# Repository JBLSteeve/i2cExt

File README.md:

# i2cExt
# 
# Jeedom plugin for XplDuino boards
# 	based on IPX800 design
# 	based on JeePlcBus daemon
# 
# Thanks to Ikes7200 and PFrank1990

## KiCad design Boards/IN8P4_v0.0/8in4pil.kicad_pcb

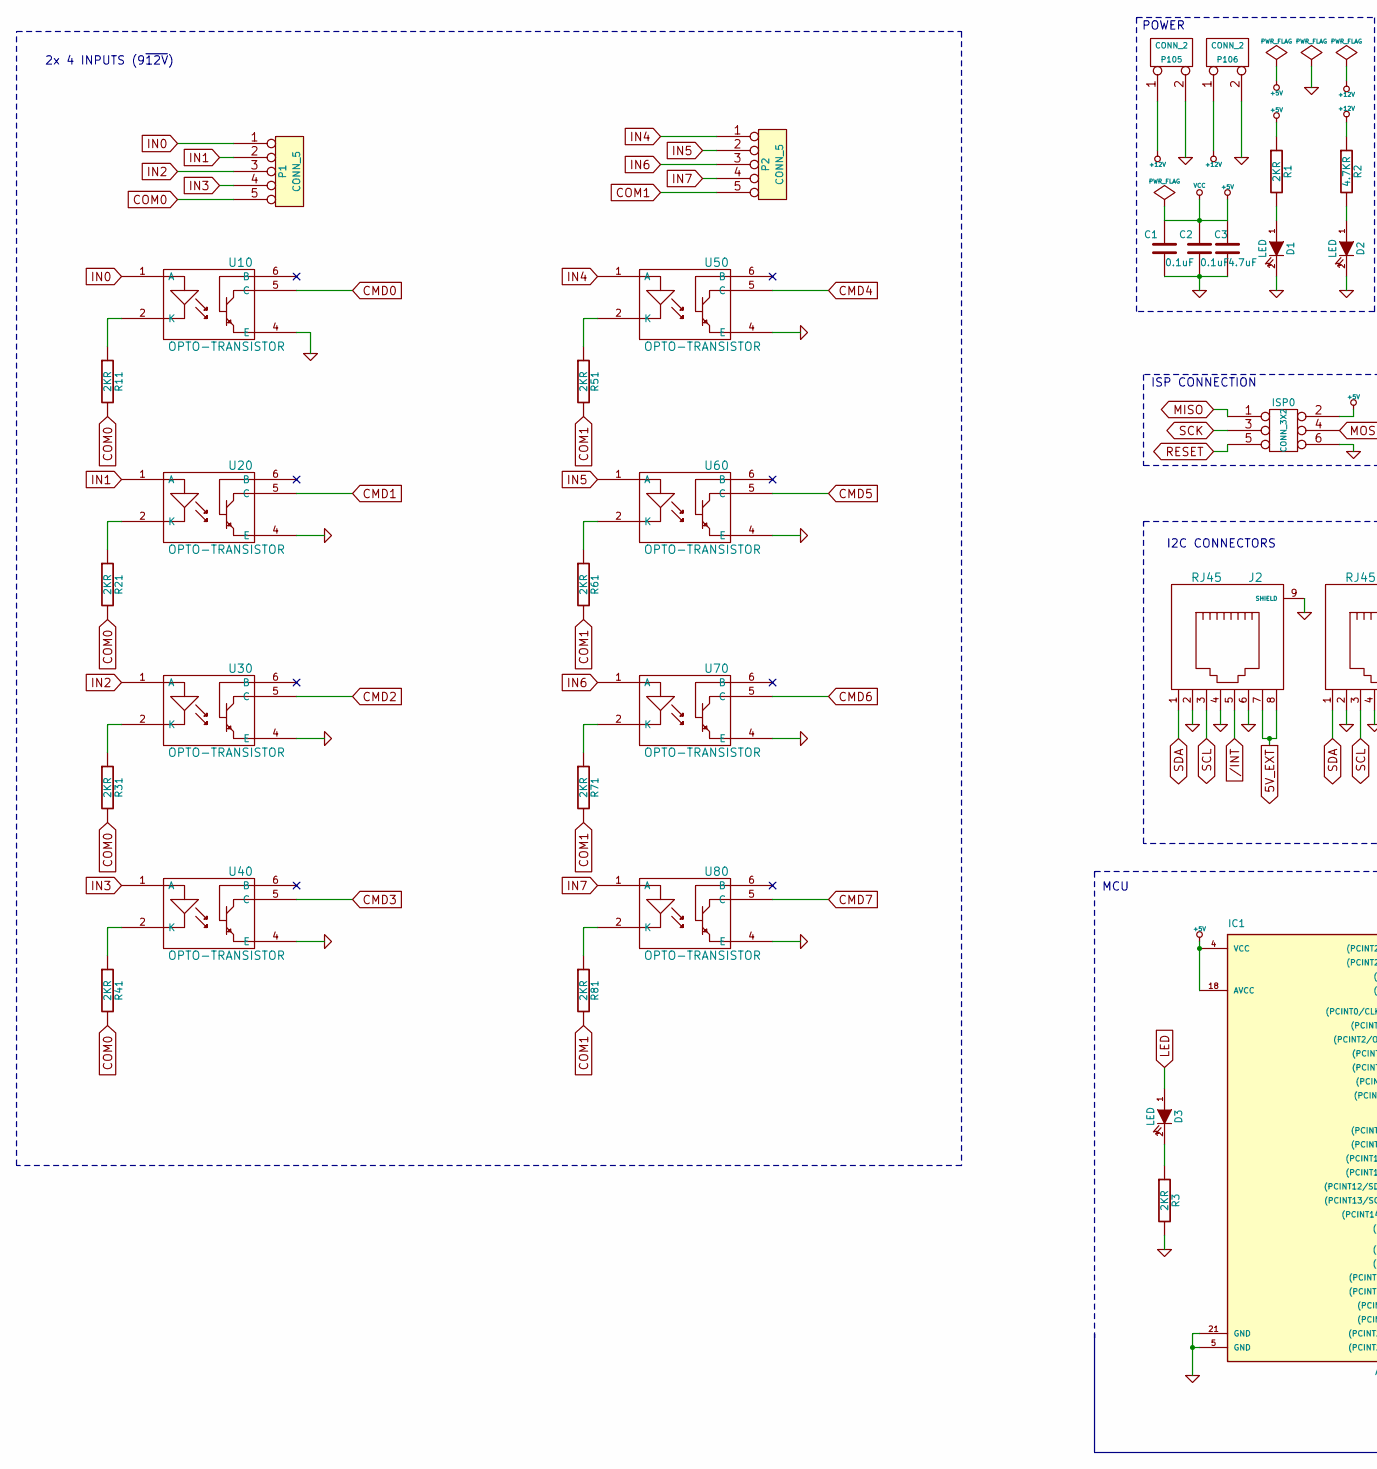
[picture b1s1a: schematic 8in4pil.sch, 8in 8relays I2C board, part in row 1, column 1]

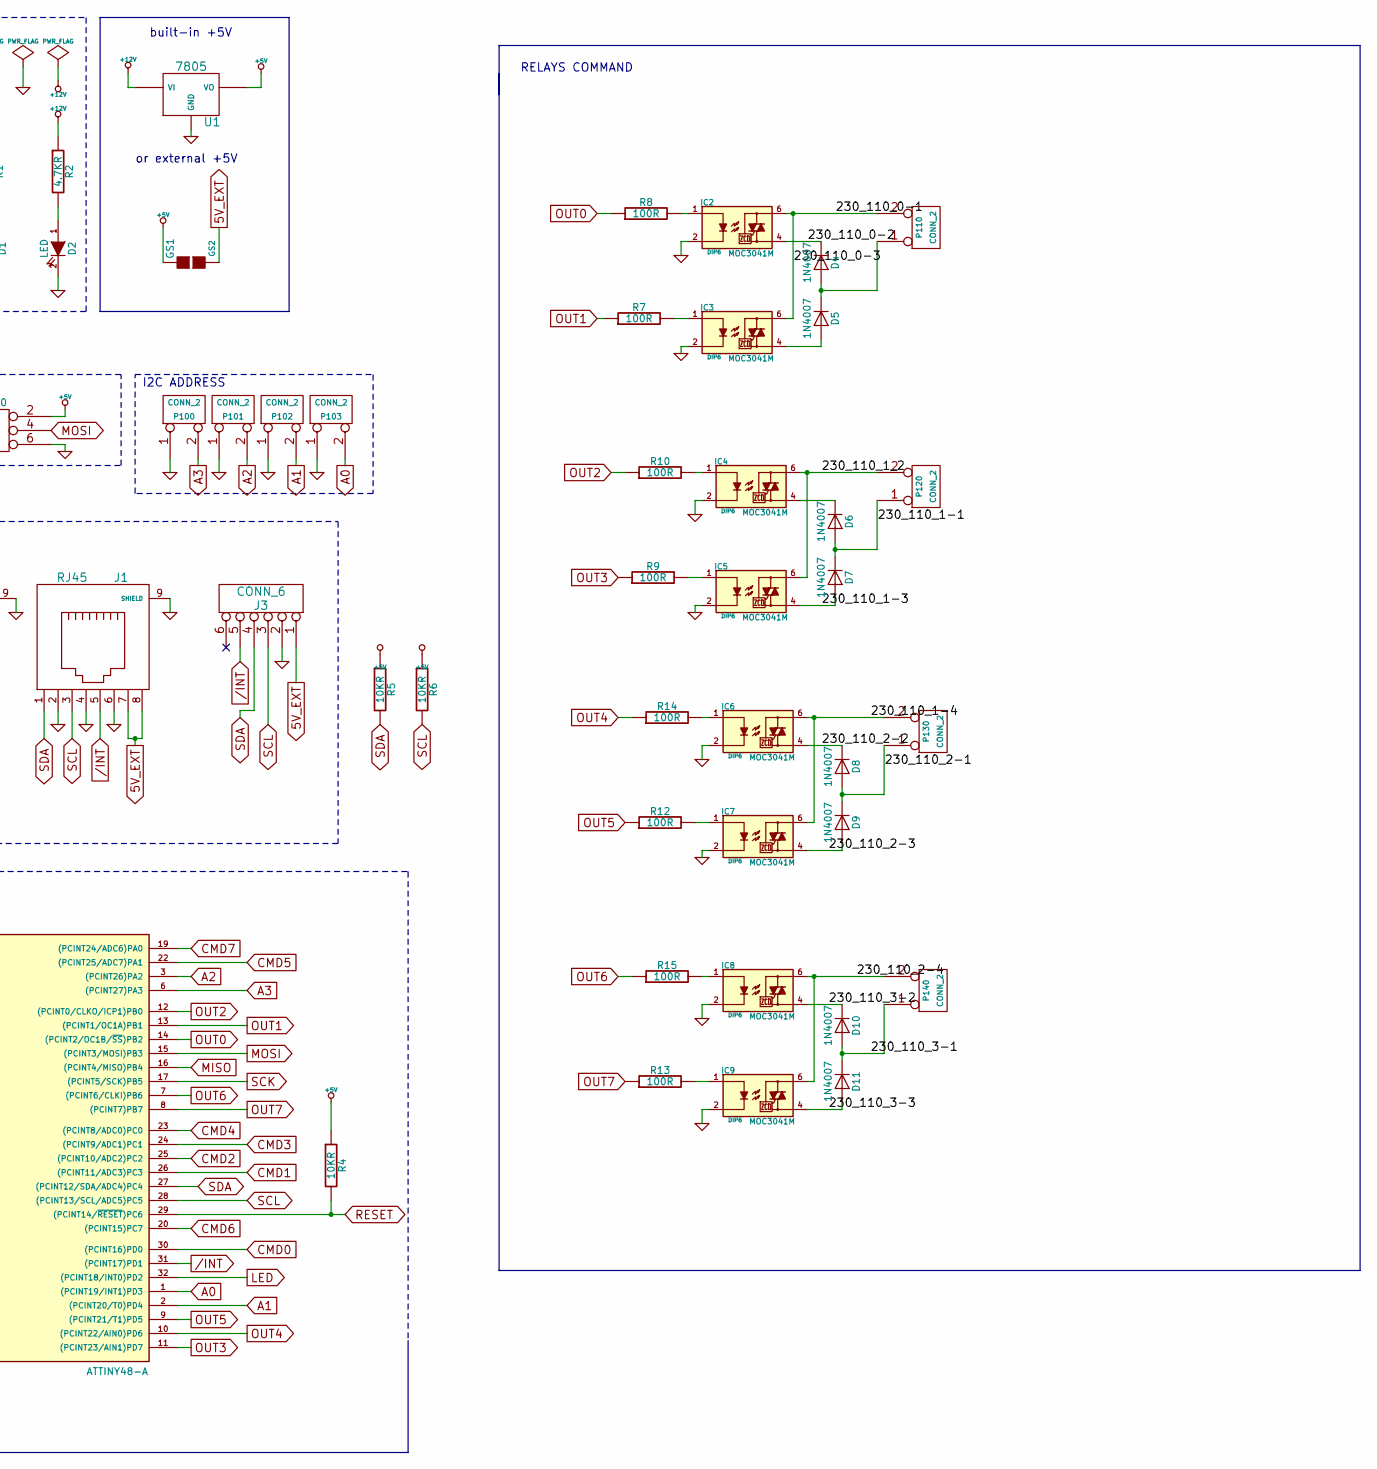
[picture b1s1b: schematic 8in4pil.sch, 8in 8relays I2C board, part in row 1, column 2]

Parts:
C1, C2: 0.1uF
C3: 4.7uF
D1, D2, D3: LED
D4, D5, D6, D7, D8, D9, D10, D11: 1N4007; D_DO-41_SOD81_P10.16mm_Horizontal
GS1: GS2
IC1: ATTINY48-A; TQFP32
IC2, IC3, IC4, IC5, IC6, IC7, IC8, IC9: MOC3041M; DIP6
ISP0: CONN_3X2
J1, J2: RJ45
J3: CONN_6
P1, P2: CONN_5
P100, P101, P102, P103, P105, P106, P110, P120, P130, P140: CONN_2
R1, R3, R11, R21, R31, R41, R51, R61, R71, R81: 2KR
R2: 4.7KR
R4, R5, R6: 10KR
R7, R8, R9, R10, R12, R13, R14, R15: 100R
U1: 7805
U10, U20, U30, U40, U50, U60, U70, U80: OPTO-TRANSISTOR

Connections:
5V_EXT: GS1.2 (G2), J1.7, J1.8, J2.7, J2.8, J3.1
+5V: C1.1, C2.1, C3.1, GS1.1 (G1), IC1.4 (VCC), IC1.18 (AVCC), ISP0.2, R1.1, R4.1, R5.1, R6.1, U1.VO
+12V: P105.1, P106.1, R2.1, U1.VI
/230_110_0-1: IC2.6, IC3.6, P110.2 (PM)
/230_110_0-2: D4.1 (K), IC2.4
/230_110_1-1: D6.2 (A), D7.1 (K), P120.1
/230_110_1-3: D7.2 (A), IC5.4
/230_110_1-4: IC6.6, IC7.6, P130.2 (PM)
/230_110_1_2: IC4.6, IC5.6, P120.2 (PM)
/230_110_2-1: D8.2 (A), D9.1 (K), P130.1
/230_110_2-2: D8.1 (K), IC6.4
/230_110_2-3: D9.2 (A), IC7.4
/230_110_2-4: IC8.6, IC9.6, P140.2 (PM)
/230_110_3-1: D10.2 (A), D11.1 (K), P140.1
/230_110_3-2: D10.1 (K), IC8.4
/230_110_3-3: D11.2 (A), IC9.4
/INT: IC1.31 ((PCINT17)PD1), J1.5, J2.5, J3.5
A0: IC1.1 ((PCINT19/INT1)PD3), P103.2 (PM)
A1: IC1.2 ((PCINT20/T0)PD4), P102.2 (PM)
A2: IC1.3 ((PCINT26)PA2), P101.2 (PM)
A3: IC1.6 ((PCINT27)PA3), P100.2 (PM)
CMD0: IC1.30 ((PCINT16)PD0), U10.5 (C)
CMD1: IC1.26 ((PCINT11/ADC3)PC3), U20.5 (C)
CMD2: IC1.25 ((PCINT10/ADC2)PC2), U30.5 (C)
CMD3: IC1.24 ((PCINT9/ADC1)PC1), U40.5 (C)
CMD4: IC1.23 ((PCINT8/ADC0)PC0), U50.5 (C)
CMD5: IC1.22 ((PCINT25/ADC7)PA1), U60.5 (C)
CMD6: IC1.20 ((PCINT15)PC7), U70.5 (C)
CMD7: IC1.19 ((PCINT24/ADC6)PA0), U80.5 (C)
COM0: P1.5, R11.2, R21.2, R31.2, R41.2
COM1: P2.5, R51.2, R61.2, R71.2, R81.2
GND: C1.2, C2.2, C3.2, D1.2 (K), D2.2 (K), IC1.5 (GND), IC1.21 (GND), IC2.2, IC3.2, IC4.2, IC5.2, IC6.2, IC7.2, IC8.2, IC9.2, ISP0.6, J1.2, J1.4, J1.6, J1.9 (SHIELD), J2.2, J2.4, J2.6, J2.9 (SHIELD), J3.2, P100.1, P101.1, P102.1, P103.1, P105.2 (PM), P106.2 (PM), R3.2, U1.GND, U10.4 (E), U20.4 (E), U30.4 (E), U40.4 (E), U50.4 (E), U60.4 (E), U70.4 (E), U80.4 (E)
IN0: P1.1, U10.1 (A)
IN1: P1.2, U20.1 (A)
IN2: P1.3, U30.1 (A)
IN3: P1.4, U40.1 (A)
IN4: P2.1, U50.1 (A)
IN5: P2.2, U60.1 (A)
IN6: P2.3, U70.1 (A)
IN7: P2.4, U80.1 (A)
LED: D3.1 (A), IC1.32 ((PCINT18/INT0)PD2)
MISO: IC1.16 ((PCINT4/MISO)PB4), ISP0.1
MOSI: IC1.15 ((PCINT3/MOSI)PB3), ISP0.4
unnamed: IC8.1, R15.2
unnamed: IC9.1, R13.2
unnamed: D4.2 (A), D5.1 (K), P110.1
unnamed: D5.2 (A), IC3.4
unnamed: D6.1 (K), IC4.4
unnamed: IC2.1, R8.2
unnamed: IC3.1, R7.2
unnamed: IC4.1, R10.2
unnamed: IC5.1, R9.2
unnamed: IC7.1, R12.2
unnamed: IC6.1, R14.2
unnamed: R61.1, U60.2 (K)
unnamed: R71.1, U70.2 (K)
unnamed: R81.1, U80.2 (K)
unnamed: R41.1, U40.2 (K)
unnamed: R51.1, U50.2 (K)
unnamed: D3.2 (K), R3.1
unnamed: R11.1, U10.2 (K)
unnamed: R21.1, U20.2 (K)
unnamed: R31.1, U30.2 (K)
unnamed: D2.1 (A), R2.2
unnamed: D1.1 (A), R1.2
OUT0: IC1.14 ((PCINT2/OC1B/~SS~)PB2), R8.1
OUT1: IC1.13 ((PCINT1/OC1A)PB1), R7.1
OUT2: IC1.12 ((PCINT0/CLKO/ICP1)PB0), R10.1
OUT3: IC1.11 ((PCINT23/AIN1)PD7), R9.1
OUT4: IC1.10 ((PCINT22/AIN0)PD6), R14.1
OUT5: IC1.9 ((PCINT21/T1)PD5), R12.1
OUT6: IC1.7 ((PCINT6/CLKI)PB6), R15.1
OUT7: IC1.8 ((PCINT7)PB7), R13.1
RESET: IC1.29 ((PCINT14/~RESET~)PC6), ISP0.5, R4.2
SCK: IC1.17 ((PCINT5/SCK)PB5), ISP0.3
SCL: IC1.28 ((PCINT13/SCL/ADC5)PC5), J1.3, J2.3, J3.3, R6.2
SDA: IC1.27 ((PCINT12/SDA/ADC4)PC4), J1.1, J2.1, J3.4, R5.2

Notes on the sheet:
ISP CONNECTION
I2C ADDRESS
POWER
I2C CONNECTORS
MCU
built-in +5V
or external +5V
RELAYS COMMAND
2x 4 INPUTS (9~12V)

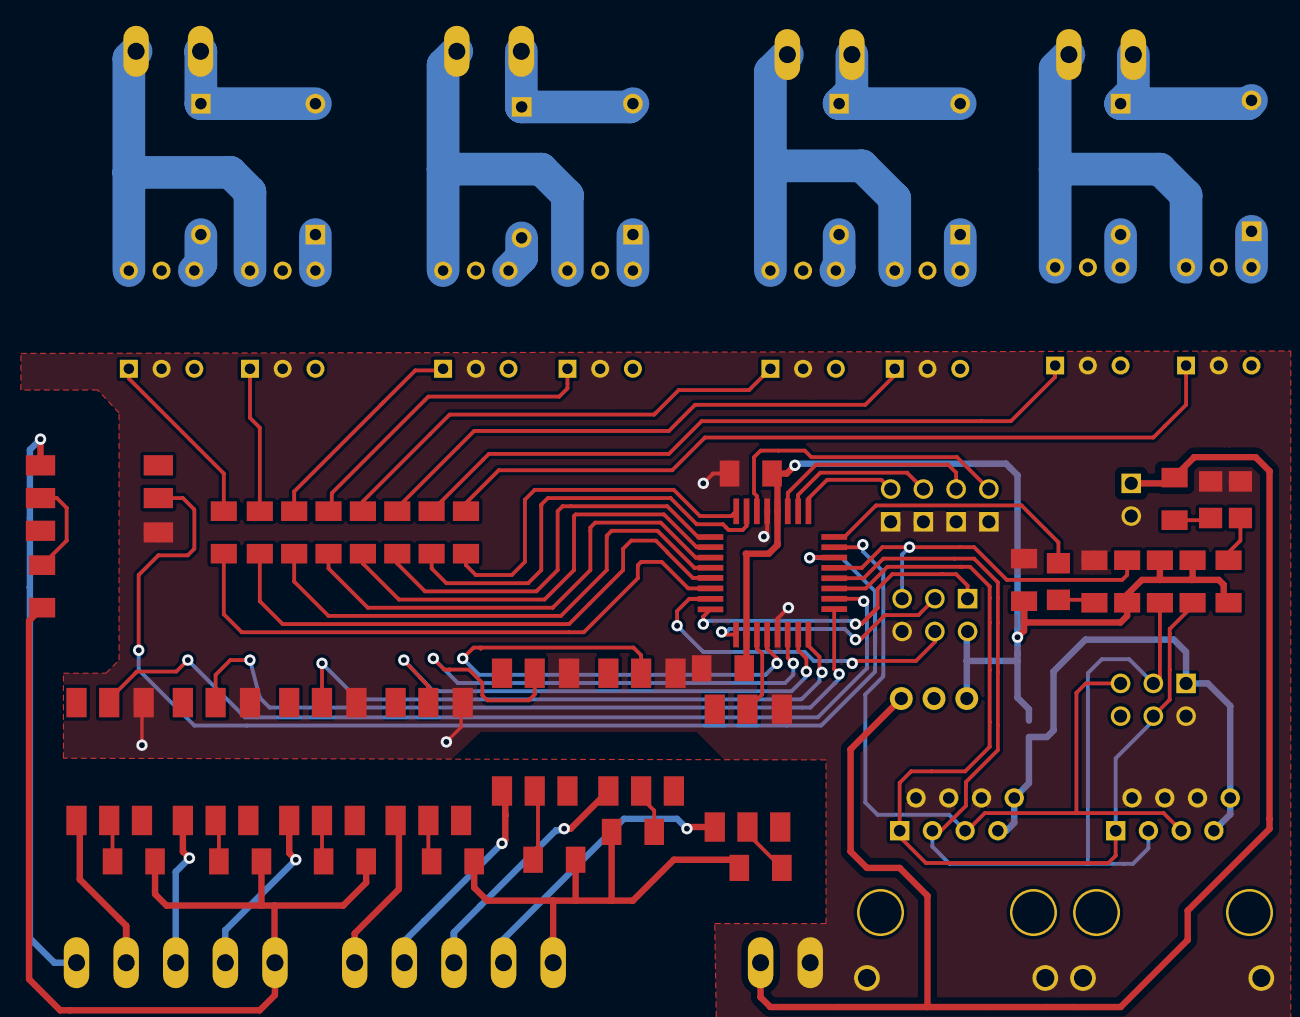
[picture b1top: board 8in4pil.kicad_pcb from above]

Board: 2 copper layers, 71 parts (0 on the bottom side), 77 nets.

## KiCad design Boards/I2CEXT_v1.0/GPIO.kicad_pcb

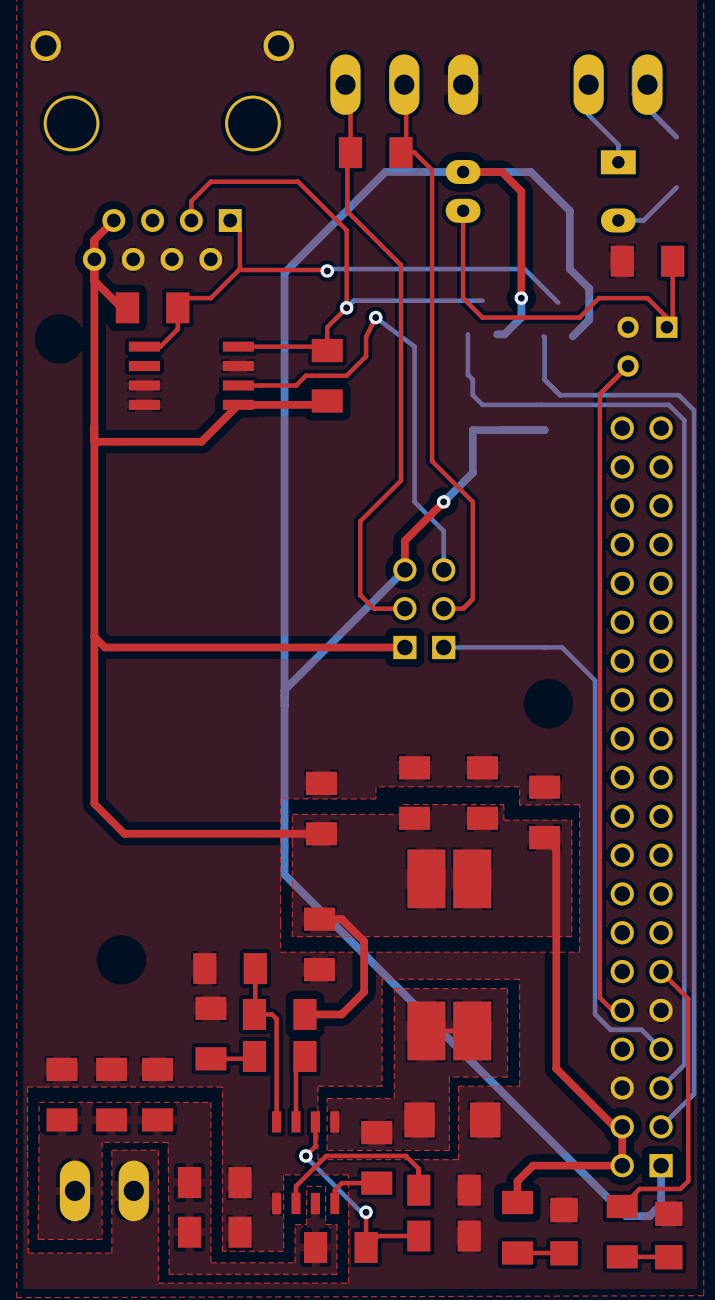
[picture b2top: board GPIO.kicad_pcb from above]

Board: 2 copper layers, 44 parts (0 on the bottom side), 27 nets.

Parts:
1Wire: CONN_3; MOL_CONN_3_MINI
C301, C303, C304, C310, C311: 1uF; SM1206
C302: 150pF; SM1206POL
C305, C306, C307, C308, C312: 4.7uF; SM1206
C309: 100nF; SM1206
D101, D102: LED; LED-1206
D301: B280-13-F; B290-13-F
IC2: DS2482-100S; 1wire-SO08
J1: Raspberry_Pi_2_3; PIN_ARRAY_20X2
J101: RJ45; RJ45_BASIC
L301: SRF1260-150M
POWER1: CONN_2; MOL_CONN_2_MINI
Q1: BS170; TO92
Q2, Q3: BSS138; SOT23
R1, R102: 3.3kR; SM1206
R2, R4, R5, R7, R106: 10kR; SM1206
R3: 4.7kR; SM1206
R200: 4.7k; SM1206
R301: 17.4k; SM1206
R302: 100k; SM1206
R303: 200k; SM1206
R304: 158k; SM1206
R305: 40.2k; SM1206
R306: 210k; SM1206
Sel_1w, Sel_1w-Pwr: CONN_3; PIN_ARRAY_3X1
TELEINFO: CONN_2; MOL_CONN_2_MINI
U1: LTV-814; OPTORESISTOR_NSL-32
U302: MP2562DS; SO8E

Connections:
1WIRE: J1.7, Sel_1w.1
1WireOut_2: IC2.2, Sel_1w.3
3.3V: J1.1, Q2.1, Q3.1, R4.2, R5.2, Sel_1w-Pwr.3, U1.4
+5V: C305.1, C306.1, C307.1, C308.1, C312.1, IC2.1, J1.2, J1.4, J101.7, J101.8, L301.3, L301.4, R1.1, R7.1, R106.1, R306.2, Sel_1w-Pwr.1
+12V: C301.1, C303.1, C304.1, C310.1, C311.1, POWER1.1, R302.1, U302.7
GND: 1Wire.1, C301.2, C303.2, C304.2, C305.2, C306.2, C307.2, C308.2, C310.2, C311.2, C312.2, D101.2, D102.2, D301.1, IC2.3, IC2.7, IC2.8, J1.6, J1.9, J101.2, J101.4, J101.6, J101.9, POWER1.2, Q1.2, R2.2, R301.2, R303.2, R304.2, R305.2, U302.5
LED_STATUS: J1.11, R102.1
unnamed: D102.1, R1.2
unnamed: 1Wire.3, R200.2, Sel_1w-Pwr.2
unnamed: 1Wire.2, R200.1, Sel_1w.2
unnamed: D101.1, R102.2
unnamed: R3.2, U1.2
unnamed: Q1.1, R2.1, U1.3
unnamed: R3.1, TELEINFO.1
unnamed: TELEINFO.2, U1.1
unnamed: C302.1, U302.3
unnamed: R303.1, U302.6
unnamed: C309.1, U302.8
unnamed: R305.1, R306.1, U302.4
unnamed: C302.2, R304.1
unnamed: R301.1, R302.2, U302.2
SCL_3.3V: J1.5, Q2.2, R4.1
SCL_5V: IC2.4, J101.3, Q2.3, R106.2
SDA_3.3V: J1.3, Q3.2, R5.1
SDA_5V: IC2.5, J101.1, Q3.3, R7.2
TELEINFO_RX: J1.10, Q1.3
pre_5V: C309.2, D301.2, L301.1, L301.2, U302.1

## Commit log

2018-09-11 First test version
    First version to make test with IN8R8 board
2018-09-11 Include register inside cards class
2018-09-11 Change return type of findCardAddress
    From table index (integer) to a cards object.
2018-09-17 Divers corrections
2018-09-17 dev version
2018-09-18 Correction pour les liens Todo gestion de la communication des cartes
2018-09-19 Exception management
2018-09-20 Create CARDS abstract method
    Create abstract methods readCardInput, readCardOutput, write.
    This should prevent error when calling read_i2cbus and write_i2cbus with a CARDS class
2018-09-20 Add docstring to cards method
2018-09-24 Create ComOK Property
    Change clearComIsOK and setComIsOK function into a property of CARDS class. See #4.
2018-09-27 Add pulse counter correct navigation to bouton configuration
2018-09-28 Cherrypick "Add pulse counter"
    8d04b326af67ae2ed498ddea63760c5d1d2bd6fa
2018-09-28 Correct merge Issues
2018-10-01 correct issues
2018-10-06 Update for input reply on daemon
2018-10-07 Update for I2C adress selection (in progress)
2018-10-07 Update for I2C address selection (in progress 2)
2018-10-08 Add task to manage hearbit
    TEST NEEDED
    Close #3
2018-10-08 Update for I2C address selection (in progress 3)
2018-10-08 Update for I2C address selection (in progress 4)
2018-10-08 Update for I2C address selection (in progress 5)
2018-10-09 Typo correction
2018-10-10 Start thread...
2018-10-10 Multi-task added
2018-10-29 Add the IN4DIM4 board
    Runing version with 2 boards (IN8R8 and IN4DIM4)
2018-10-30 Correct CPU issue and add STOP command for dimmer
2018-11-14 add the board IN8P4
2018-11-20 Add install modules
2018-11-28 Correct type for jeedom widget
2019-02-01 indentation

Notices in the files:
Boards/I2CEXT_v1.0/GPIO.kicad_pcb:
GNU GPL v2
